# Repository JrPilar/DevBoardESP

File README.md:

# DevBoardESP
Dev Board based on ESP32-S3-WROOM2 chip to controll equatorial mount for telescope.  
Project made in KiCad6, for future printing. Board is architectured for future versions of ArduinoEQ, which will include autofocus motor, onboard RTC, GOTO etc.
Board is powered by 12V, has an USB-C port for COM port and programable NeoPixel.

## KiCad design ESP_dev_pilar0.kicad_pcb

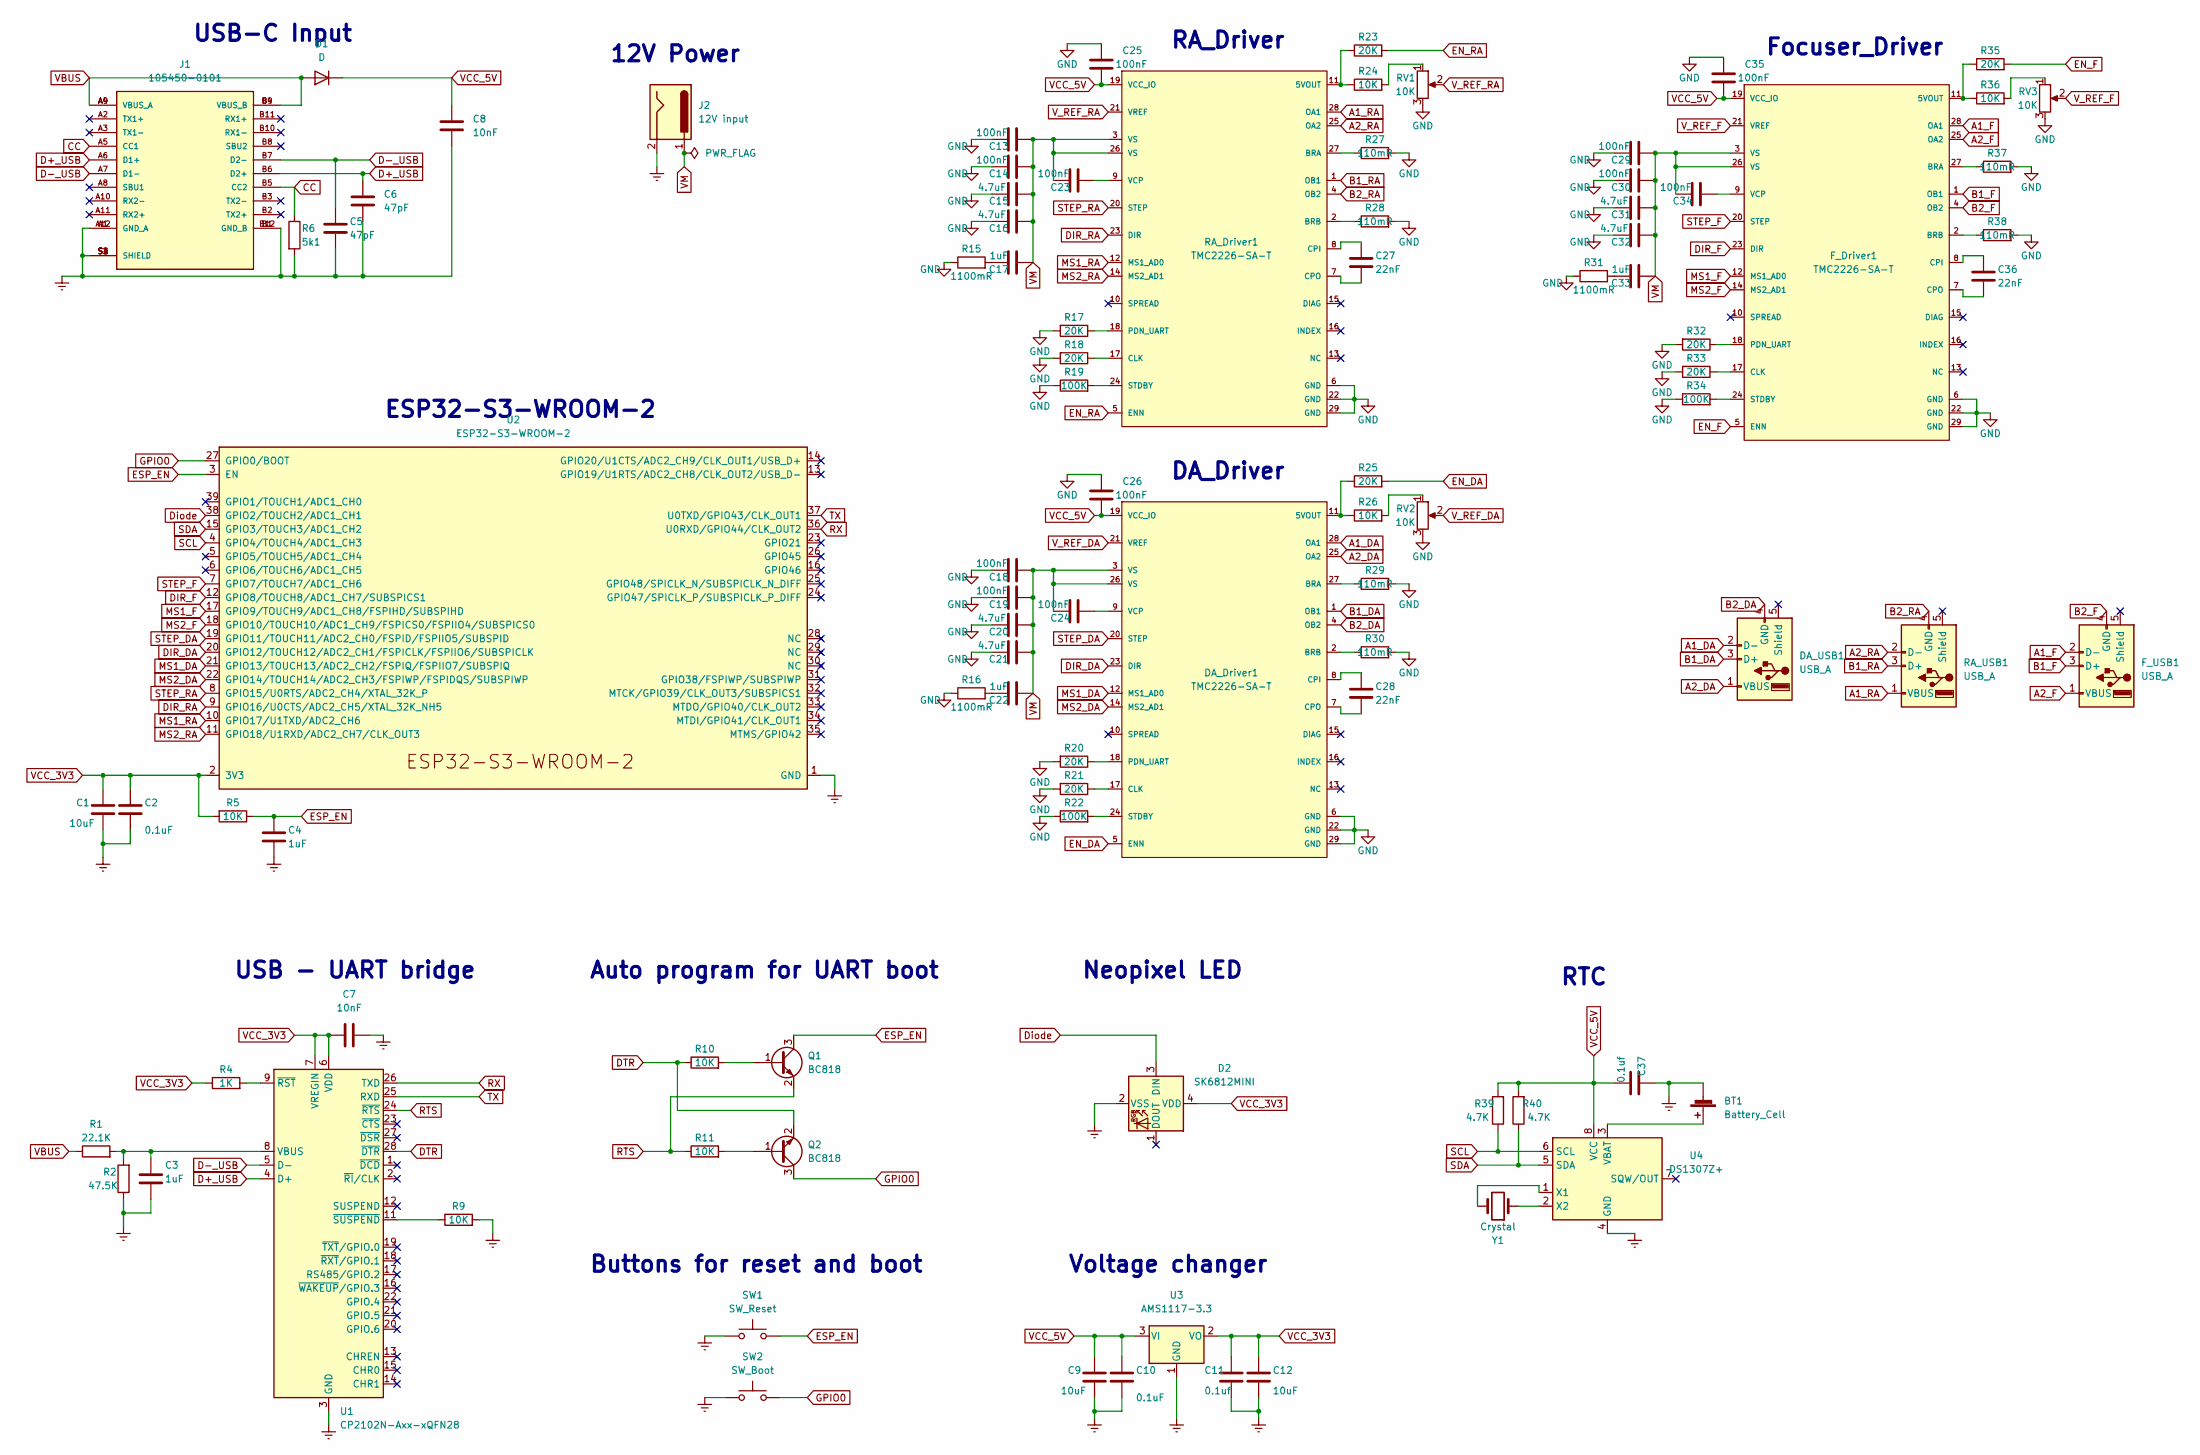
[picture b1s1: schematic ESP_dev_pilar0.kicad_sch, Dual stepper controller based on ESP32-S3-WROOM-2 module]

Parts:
BT1: Battery_Cell; BatteryHolder_Keystone_1057_1x2032
C1, C9, C12: 10uF; C_1210_3225Metric
C2, C10: 0.1uF; C_0603_1608Metric
C3, C4, C17, C22, C33: 1uF; C_0603_1608Metric
C5, C6: 47pF; C_0603_1608Metric
C7, C8: 10nF; C_0603_1608Metric
C11: 0.1uf; C_0603_1608Metric
C13, C14, C18, C19, C23, C24, C25, C26, C29, C30, C34, C35: 100nF; C_0603_1608Metric
C15, C16, C20, C21, C31, C32: 4.7uF; C_0603_1608Metric
C27, C28, C36: 22nF; C_0603_1608Metric
C37: 0.1uf; C_1210_3225Metric
D1: D; D_SOD-323
D2: SK6812MINI; LED_SK6812MINI_PLCC4_3.5x3.5mm_P1.75mm
DA_Driver1: TMC2226-SA-T; Trinamic-TMC2226-SA-T-IPC_B; mouser part number 700-TMC2226-SA-T; digikey description IC MTR DRV 4.75-29V HTSSOP28
DA_USB1: USB_A; USB_A_Molex_67643_Horizontal
F_Driver1: TMC2226-SA-T; Trinamic-TMC2226-SA-T-IPC_B; mouser part number 700-TMC2226-SA-T; digikey description IC MTR DRV 4.75-29V HTSSOP28
F_USB1: USB_A; USB_A_Molex_67643_Horizontal
J1: 105450-0101; USB_C_Receptacle_Molex_105450-0101; PARTREV A7
J2: 12V input; BarrelJack_Horizontal
Q1, Q2: BC818; SOT-23
R1: 22.1K; R_0603_1608Metric_Pad0.98x0.95mm_HandSolder
R2: 47.5K; R_0603_1608Metric_Pad0.98x0.95mm_HandSolder
R4: 1K; R_0603_1608Metric_Pad0.98x0.95mm_HandSolder
R5, R9, R10, R11: 10K; R_0603_1608Metric_Pad0.98x0.95mm_HandSolder
R6: 5k1; R_0603_1608Metric_Pad0.98x0.95mm_HandSolder
R15, R16, R31: 1100mR; R_1206_3216Metric_Pad1.30x1.75mm_HandSolder
R17, R18, R20, R21, R23, R25, R32, R33, R35: 20K; R_1206_3216Metric_Pad1.30x1.75mm_HandSolder
R19, R22, R34: 100K; R_1206_3216Metric_Pad1.30x1.75mm_HandSolder
R24, R26, R36: 10K; R_1206_3216Metric_Pad1.30x1.75mm_HandSolder
R27, R28, R29, R30, R37, R38: 110mR; R_0805_2012Metric_Pad1.20x1.40mm_HandSolder
R39, R40: 4.7K; R_0603_1608Metric_Pad0.98x0.95mm_HandSolder
RA_Driver1: TMC2226-SA-T; Trinamic-TMC2226-SA-T-IPC_B; mouser part number 700-TMC2226-SA-T; digikey description IC MTR DRV 4.75-29V HTSSOP28
RA_USB1: USB_A; USB_A_Molex_67643_Horizontal
RV1, RV2, RV3: 10K; Potentiometer_Bourns_TC33X_Vertical
SW1: SW_Reset; SW_Push_1P1T_NO_6x6mm_H9.5mm
SW2: SW_Boot; SW_Push_1P1T_NO_6x6mm_H9.5mm
U1: CP2102N-Axx-xQFN28; QFN-28-1EP_5x5mm_P0.5mm_EP3.35x3.35mm
U2: ESP32-S3-WROOM-2
U3: AMS1117-3.3; SOT-223-3_TabPin2
U4: DS1307Z+; SOIC-8_3.9x4.9mm_P1.27mm
Y1: Crystal; Crystal_DS26_D2.0mm_L6.0mm_Vertical

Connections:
A1_DA: DA_Driver1.28 (OA1), DA_USB1.2 (D-)
A1_F: F_Driver1.28 (OA1), F_USB1.2 (D-)
A1_RA: RA_Driver1.28 (OA1), RA_USB1.1 (VBUS)
A2_DA: DA_Driver1.25 (OA2), DA_USB1.1 (VBUS)
A2_F: F_Driver1.25 (OA2), F_USB1.1 (VBUS)
A2_RA: RA_Driver1.25 (OA2), RA_USB1.2 (D-)
B1_DA: DA_Driver1.1 (OB1), DA_USB1.3 (D+)
B1_F: F_Driver1.1 (OB1), F_USB1.3 (D+)
B1_RA: RA_Driver1.1 (OB1), RA_USB1.3 (D+)
B2_DA: DA_Driver1.4 (OB2), DA_USB1.4 (GND)
B2_F: F_Driver1.4 (OB2), F_USB1.4 (GND)
B2_RA: RA_Driver1.4 (OB2), RA_USB1.4 (GND)
CC: J1.A5 (CC1), J1.B5 (CC2), R6.1
D+_USB: C6.1, J1.A6 (D1+), J1.B6 (D2+), U1.4 (D+)
D-_USB: C5.2, J1.A7 (D1-), J1.B7 (D2-), U1.5 (D-)
DIR_DA: DA_Driver1.23 (DIR), U2.20 (GPIO12/TOUCH12/ADC2_CH1/FSPICLK/FSPIIO6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)
DIR_F: F_Driver1.23 (DIR), U2.12 (GPIO8/TOUCH8/ADC1_CH7/SUBSPICS1)
DIR_RA: RA_Driver1.23 (DIR), U2.9 (GPIO16/U0CTS/ADC2_CH5/XTAL_32K_NH5)
DTR: Q2.2 (E), R10.1, U1.28 (~DTR)
Diode: D2.3 (DIN), U2.38 (GPIO2/TOUCH2/ADC1_CH1)
EN_DA: DA_Driver1.5 (ENN), R25.2
EN_F: F_Driver1.5 (ENN), R35.2
EN_RA: R23.2, RA_Driver1.5 (ENN)
ESP_EN: C4.1, Q1.3 (C), R5.1, SW1.2, U2.3 (EN)
Earth: BT1.2 (-), C1.2, C2.2, C3.1, C4.2, C5.1, C6.2, C7.2, C8.2, C9.2, C10.2, C11.2, C12.2, C37.1, D2.2 (VSS), J1.A1 (GND_A), J1.A12 (GND_A), J1.B1 (GND_B), J1.B12 (GND_B), J1.S1 (SHIELD), J1.S2 (SHIELD), J1.S3 (SHIELD), J1.S4 (SHIELD), J2.2, R2.1, R6.2, R9.2, SW1.1, SW2.1, U1.3 (GND), U1.29 (GND), U2.1 (GND), U2.40 (GND), U2.41 (GND), U3.1 (GND), U4.4 (GND)
GND: C13.1, C14.1, C15.1, C16.1, C18.1, C19.1, C20.1, C21.1, C25.1, C26.1, C29.1, C30.1, C31.1, C32.1, C35.1, DA_Driver1.6 (GND), DA_Driver1.22 (GND), DA_Driver1.29 (GND), F_Driver1.6 (GND), F_Driver1.22 (GND), F_Driver1.29 (GND), R15.1, R16.1, R17.2, R18.2, R19.1, R20.2, R21.2, R22.1, R27.2, R28.2, R29.2, R30.2, R31.1, R32.2, R33.2, R34.1, R37.2, R38.2, RA_Driver1.6 (GND), RA_Driver1.22 (GND), RA_Driver1.29 (GND), RV1.3, RV2.3, RV3.3
GPIO0: Q2.3 (C), SW2.2, U2.27 (GPIO0/BOOT)
MS1_DA: DA_Driver1.12 (MS1_AD0), U2.21 (GPIO13/TOUCH13/ADC2_CH2/FSPIQ/FSPIIO7/S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)
MS1_F: F_Driver1.12 (MS1_AD0), U2.17 (GPIO9/TOUCH9/ADC1_CH8/FSPIHD/SUBSPIHD)
MS1_RA: RA_Driver1.12 (MS1_AD0), U2.10 (GPIO17/U1TXD/ADC2_CH6)
MS2_DA: DA_Driver1.14 (MS2_AD1), U2.22 (GPIO14/TOUCH14/ADC2_CH3/FSPIWP/FSPIDQS/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)
MS2_F: F_Driver1.14 (MS2_AD1), U2.18 (GPIO10/TOUCH10/ADC1_CH9/FSPICS0/FSPIIO4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)
MS2_RA: RA_Driver1.14 (MS2_AD1), U2.11 (GPIO18/U1RXD/ADC2_CH7/CLK_OUT3)
unnamed: BT1.1 (+), U4.3 (VBAT)
unnamed: C17.1, R15.2
unnamed: C22.1, R16.2
unnamed: C33.1, R31.2
unnamed: DA_Driver1.11 (5VOUT), R25.1, R26.1
unnamed: DA_Driver1.27 (BRA), R29.1
unnamed: DA_Driver1.2 (BRB), R30.1
unnamed: DA_Driver1.17 (CLK), R21.1
unnamed: C28.2, DA_Driver1.8 (CPI)
unnamed: C28.1, DA_Driver1.7 (CPO)
unnamed: DA_Driver1.18 (PDN_UART), R20.1
unnamed: DA_Driver1.24 (STDBY), R22.2
unnamed: C24.2, DA_Driver1.9 (VCP)
unnamed: F_Driver1.11 (5VOUT), R35.1, R36.1
unnamed: F_Driver1.27 (BRA), R37.1
unnamed: F_Driver1.2 (BRB), R38.1
unnamed: F_Driver1.17 (CLK), R33.1
unnamed: C36.2, F_Driver1.8 (CPI)
unnamed: C36.1, F_Driver1.7 (CPO)
unnamed: F_Driver1.18 (PDN_UART), R32.1
unnamed: F_Driver1.24 (STDBY), R34.2
unnamed: C34.2, F_Driver1.9 (VCP)
unnamed: Q1.1 (B), R10.2
unnamed: Q2.1 (B), R11.2
unnamed: R24.2, RV1.1
unnamed: R26.2, RV2.1
unnamed: R36.2, RV3.1
unnamed: R23.1, R24.1, RA_Driver1.11 (5VOUT)
unnamed: R27.1, RA_Driver1.27 (BRA)
unnamed: R28.1, RA_Driver1.2 (BRB)
unnamed: R18.1, RA_Driver1.17 (CLK)
unnamed: C27.2, RA_Driver1.8 (CPI)
unnamed: C27.1, RA_Driver1.7 (CPO)
unnamed: R17.1, RA_Driver1.18 (PDN_UART)
unnamed: R19.2, RA_Driver1.24 (STDBY)
unnamed: C23.2, RA_Driver1.9 (VCP)
unnamed: C3.2, R1.2, R2.2, U1.8 (VBUS)
unnamed: R4.2, U1.9 (~RST)
unnamed: R9.1, U1.11 (~SUSPEND)
unnamed: U4.1 (X1), Y1.2
unnamed: U4.2 (X2), Y1.1
RTS: Q1.2 (E), R11.1, U1.24 (~RTS)
RX: U1.26 (TXD), U2.36 (U0RXD/GPIO44/CLK_OUT2)
SCL: R39.1, U2.4 (GPIO4/TOUCH4/ADC1_CH3), U4.6 (SCL)
SDA: R40.1, U2.15 (GPIO3/TOUCH3/ADC1_CH2), U4.5 (SDA)
STEP_DA: DA_Driver1.20 (STEP), U2.19 (GPIO11/TOUCH11/ADC2_CH0/FSPID/FSPIIO5/S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)
STEP_F: F_Driver1.20 (STEP), U2.7 (GPIO7/TOUCH7/ADC1_CH6)
STEP_RA: RA_Driver1.20 (STEP), U2.8 (GPIO15/U0RTS/ADC2_CH4/XTAL_32K_P)
TX: U1.25 (RXD), U2.37 (U0TXD/GPIO43/CLK_OUT1)
VBUS: D1.2 (A), J1.A4 (VBUS_A), J1.A9 (VBUS_A), J1.B4 (VBUS_B), J1.B9 (VBUS_B), R1.1
VCC_3V3: C1.1, C2.1, C7.1, C11.1, C12.1, D2.4 (VDD), R4.1, R5.2, U1.6 (VDD), U1.7 (VREGIN), U2.2 (3V3), U3.2 (VO)
VCC_5V: C8.1, C9.1, C10.1, C25.2, C26.2, C35.2, C37.2, D1.1 (K), DA_Driver1.19 (VCC_IO), F_Driver1.19 (VCC_IO), R39.2, R40.2, RA_Driver1.19 (VCC_IO), U3.3 (VI), U4.8 (VCC)
VM: C13.2, C14.2, C15.2, C16.2, C17.2, C18.2, C19.2, C20.2, C21.2, C22.2, C23.1, C24.1, C29.2, C30.2, C31.2, C32.2, C33.2, C34.1, DA_Driver1.3 (VS), DA_Driver1.26 (VS), F_Driver1.3 (VS), F_Driver1.26 (VS), J2.1, RA_Driver1.3 (VS), RA_Driver1.26 (VS)
V_REF_DA: DA_Driver1.21 (VREF), RV2.2
V_REF_F: F_Driver1.21 (VREF), RV3.2
V_REF_RA: RA_Driver1.21 (VREF), RV1.2

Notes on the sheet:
RTC
Voltage changer
Auto program for UART boot
USB - UART bridge
Focuser_Driver
USB-C Input
Neopixel LED
RA_Driver
DA_Driver
Buttons for reset and boot
ESP32-S3-WROOM-2
12V Power

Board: 2 copper layers, 94 parts (0 on the bottom side), 89 nets, no tracks yet.
